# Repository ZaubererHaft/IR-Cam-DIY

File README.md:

# DIY IR Camera based on the MLX90640 IR sensor array

## Hardware

### Schematic

### Layout

### Chassis

## Software

### Display

### USB

### Sensor

### Flash

## ToDos
* Implement Config file [x]
* Fix saved image [x]
* Activate upscaling when saving image
* Implement battery level with ADC3 [x]
* Implement auto range or definable range
* Fix warnings in user_interface.c
* Replace Error_Handler with a suited dialogue

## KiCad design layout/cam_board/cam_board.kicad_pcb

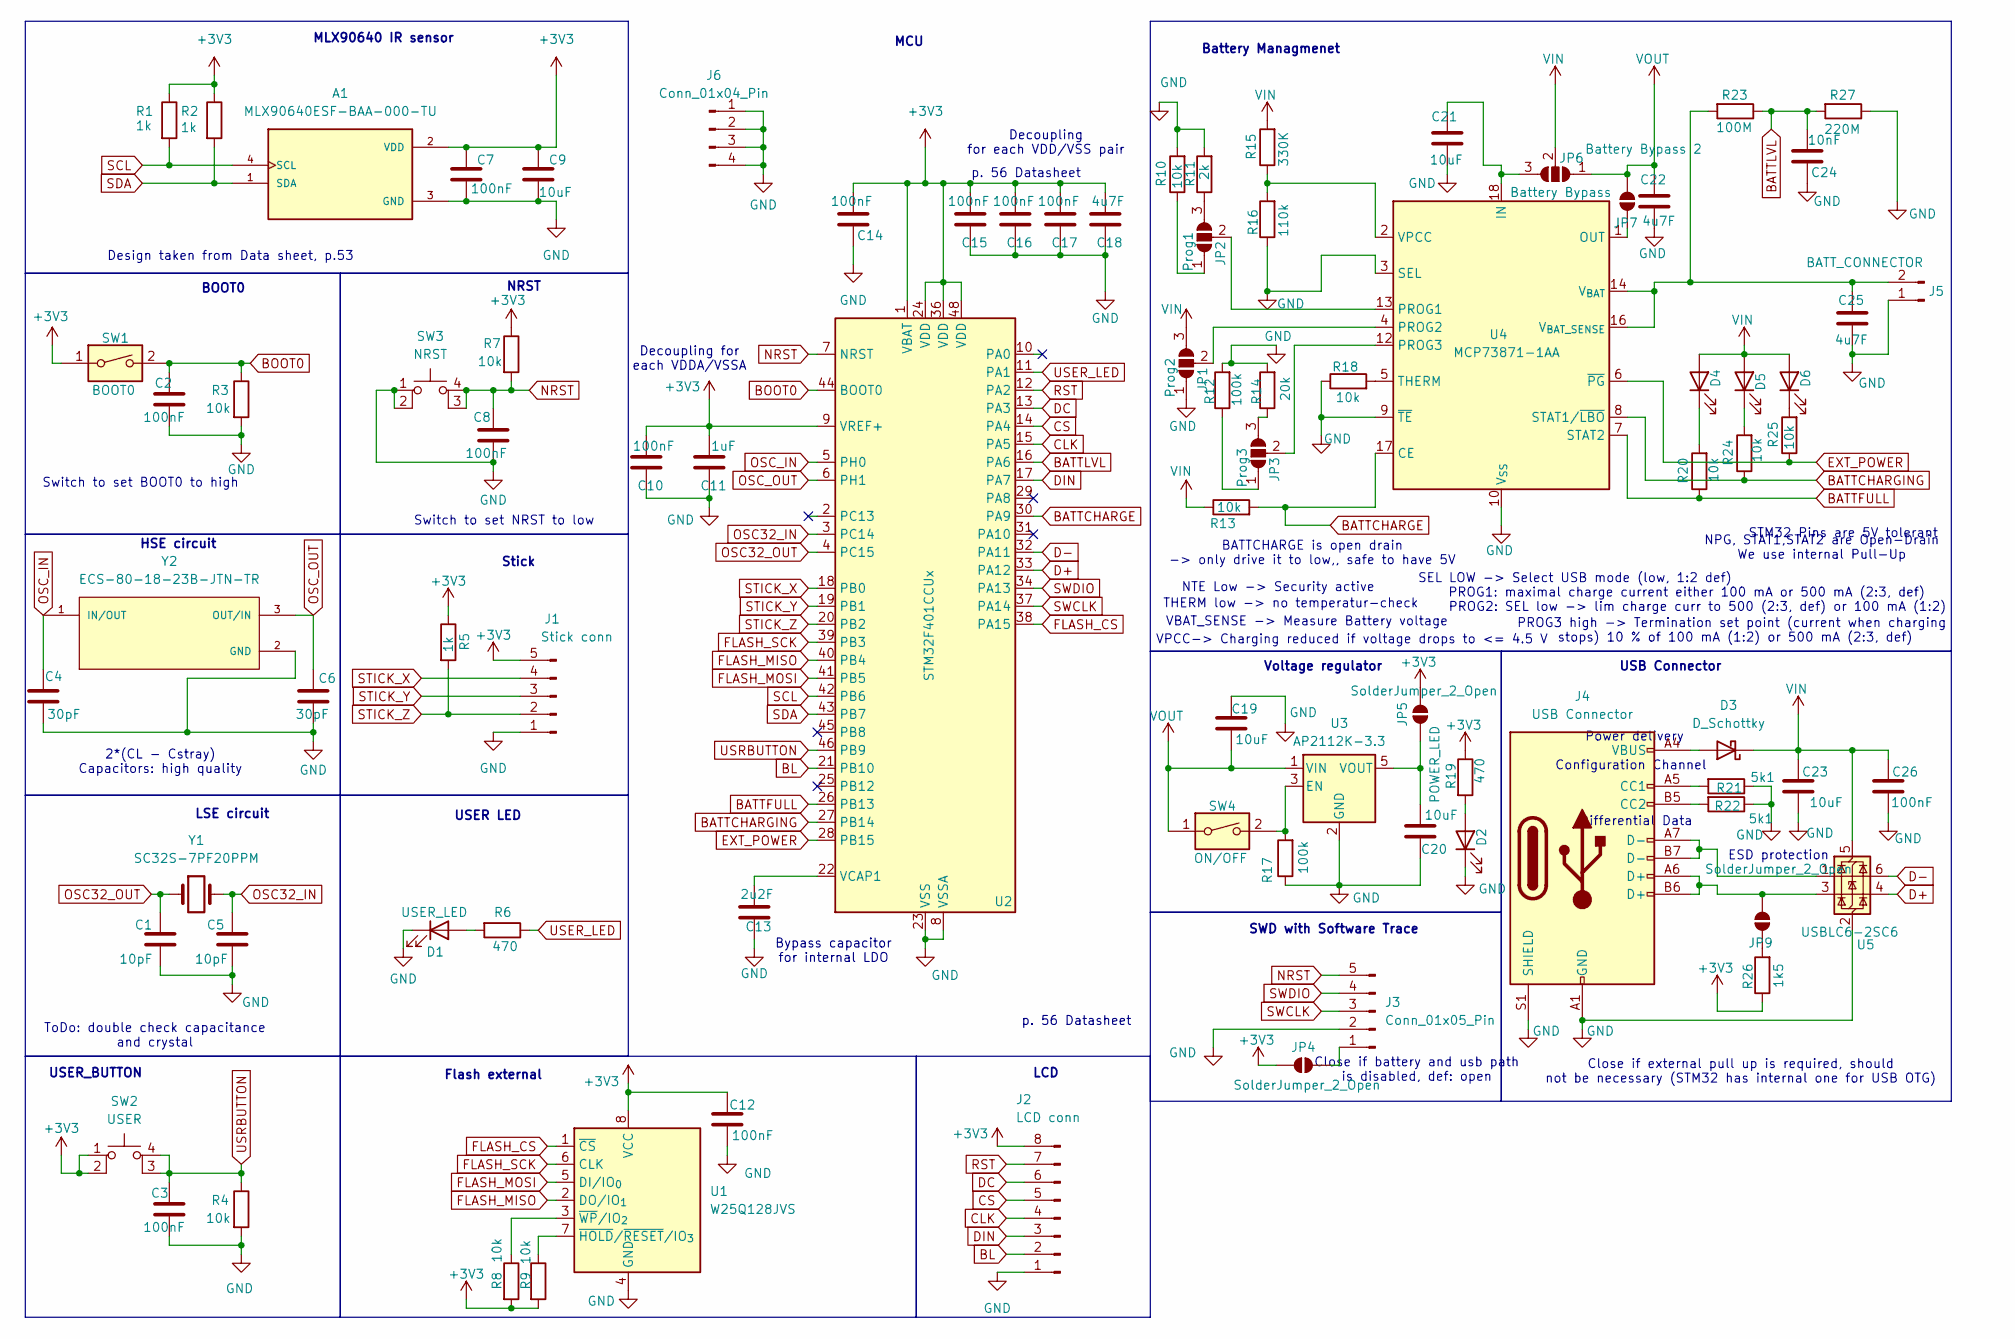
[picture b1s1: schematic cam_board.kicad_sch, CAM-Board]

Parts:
A1: MLX90640ESF-BAA-000-TU; TO292P930H600-4-MLX; PARTREV 11
C1, C5: 10pF; C_0603_1608Metric_Pad1.08x0.95mm_HandSolder
C2, C3, C7, C8, C10, C12, C14, C15, C16, C17, C26: 100nF; C_0603_1608Metric_Pad1.08x0.95mm_HandSolder
C4, C6: 30pF; C_0603_1608Metric_Pad1.08x0.95mm_HandSolder
C9, C19, C20, C21, C23: 10uF; C_0603_1608Metric_Pad1.08x0.95mm_HandSolder
C11: 1uF; C_0603_1608Metric_Pad1.08x0.95mm_HandSolder
C13: 2u2F; C_0603_1608Metric_Pad1.08x0.95mm_HandSolder
C18, C22, C25: 4u7F; C_0603_1608Metric_Pad1.08x0.95mm_HandSolder
C24: 10nF; C_0603_1608Metric_Pad1.08x0.95mm_HandSolder
D1: USER_LED; LED_0603_1608Metric_Pad1.05x0.95mm_HandSolder
D2, D4, D5, D6: POWER_LED; LED_0603_1608Metric_Pad1.05x0.95mm_HandSolder
D3: D_Schottky; D_0603_1608Metric_Pad1.05x0.95mm_HandSolder
J1: Stick conn; PinHeader_1x05_P2.54mm_Vertical
J2: LCD conn; PinHeader_1x08_P2.54mm_Vertical
J3: Conn_01x05_Pin; PinHeader_1x05_P2.54mm_Vertical
J4: USB Connector; USB_C_Receptacle_HRO_TYPE-C-31-M-12
J5: BATT_CONNECTOR; JST_PH_B2B-PH-K_1x02_P2.00mm_Vertical
J6: Conn_01x04_Pin; PinHeader_1x04_P2.54mm_Vertical
JP1: Prog2; SolderJumper-3_P1.3mm_Open_RoundedPad1.0x1.5mm_NumberLabels
JP2: Prog1; SolderJumper-3_P1.3mm_Open_RoundedPad1.0x1.5mm_NumberLabels
JP3: Prog3; SolderJumper-3_P1.3mm_Open_RoundedPad1.0x1.5mm_NumberLabels
JP4, JP5, JP9: SolderJumper_2_Open; SolderJumper-2_P1.3mm_Open_RoundedPad1.0x1.5mm
JP6: Battery Bypass; SolderJumper-3_P1.3mm_Open_RoundedPad1.0x1.5mm_NumberLabels
JP7: Battery Bypass 2; SolderJumper-2_P1.3mm_Open_RoundedPad1.0x1.5mm
R1, R2, R5: 1k; R_0603_1608Metric_Pad0.98x0.95mm_HandSolder
R3, R4, R7, R8, R9, R10, R13, R18, R20, R24, R25: 10k; R_0603_1608Metric_Pad0.98x0.95mm_HandSolder
R6, R19: 470; R_0603_1608Metric_Pad0.98x0.95mm_HandSolder
R11: 2k; R_0603_1608Metric_Pad0.98x0.95mm_HandSolder
R12, R17: 100k; R_0603_1608Metric_Pad0.98x0.95mm_HandSolder
R14: 20k; R_0603_1608Metric_Pad0.98x0.95mm_HandSolder
R15: 330K; R_0603_1608Metric_Pad0.98x0.95mm_HandSolder
R16: 110k; R_0603_1608Metric_Pad0.98x0.95mm_HandSolder
R21, R22: 5k1; R_0603_1608Metric_Pad0.98x0.95mm_HandSolder
R23: 100M; R_0603_1608Metric_Pad0.98x0.95mm_HandSolder
R26: 1k5; R_0603_1608Metric_Pad0.98x0.95mm_HandSolder
R27: 220M; R_0603_1608Metric_Pad0.98x0.95mm_HandSolder
SW1: BOOT0; SW_DIP_SPSTx01_Slide_9.78x4.72mm_W7.62mm_P2.54mm
SW2: USER; SW_1825910-6-4
SW3: NRST; SW_1825910-6-4
SW4: ON/OFF; SW_DIP_SPSTx01_Slide_9.78x4.72mm_W7.62mm_P2.54mm
U1: W25Q128JVS; SOIC-8_5.3x5.3mm_P1.27mm
U2: STM32F401CCUx; QFN-48-1EP_7x7mm_P0.5mm_EP5.6x5.6mm
U3: AP2112K-3.3; SOT-23-5_HandSoldering
U4: MCP73871-1AA; QFN-20-1EP_4x4mm_P0.5mm_EP2.5x2.5mm_ThermalVias
U5: USBLC6-2SC6; SOT-23-6_Handsoldering
Y1: SC32S-7PF20PPM; XTAL_CTS3-32.768-12.5-20-CT
Y2: ECS-80-18-23B-JTN-TR; XTAL_ECS-80-18-23B-JTN-TR

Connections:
+3V3: A1.2 (VDD), C7.2, C9.2, C10.2, C11.2, C12.2, C14.2, C15.2, C16.2, C17.2, C18.2, J1.5, J2.8, JP4.1 (A), JP5.2 (B), R1.1, R2.1, R5.1, R7.1, R8.2, R9.2, R19.1, R26.1, SW1.1, SW2.1, SW2.2, U1.8 (VCC), U2.1 (VBAT), U2.9 (VREF+), U2.24 (VDD), U2.36 (VDD), U2.48 (VDD)
BATTCHARGE: R13.2, U2.30 (PA9), U4.17 (CE)
BATTCHARGING: R24.1, U2.27 (PB14), U4.8 (STAT1/~LBO)
BATTFULL: R20.1, U2.26 (PB13), U4.7 (STAT2)
BATTLVL: C24.2, R23.1, R27.2, U2.16 (PA6)
BL: J2.2, U2.21 (PB10)
BOOT0: C2.2, R3.1, SW1.2, U2.44 (BOOT0)
CLK: J2.4, U2.15 (PA5)
CS: J2.5, U2.14 (PA4)
D+: U2.33 (PA12), U5.4 (I/O2)
D-: U2.32 (PA11), U5.6 (I/O1)
DC: J2.6, U2.13 (PA3)
DIN: J2.3, U2.17 (PA7)
EXT_POWER: R25.1, U2.28 (PB15), U4.6 (~PG)
FLASH_CS: U1.1 (~CS), U2.38 (PA15)
FLASH_MISO: U1.2 (DO/IO_{1}), U2.40 (PB4)
FLASH_MOSI: U1.5 (DI/IO_{0}), U2.41 (PB5)
FLASH_SCK: U1.6 (CLK), U2.39 (PB3)
GND: A1.3 (GND), C1.1, C2.1, C3.1, C4.1, C5.1, C6.1, C7.1, C8.1, C9.1, C10.1, C11.1, C12.1, C13.1, C14.1, C15.1, C16.1, C17.1, C18.1, C19.2, C20.2, C21.1, C22.1, C23.1, C24.1, C25.1, C26.1, D1.1 (K), D2.1 (K), J1.1, J2.1, J3.2, J4.A1 (GND), J4.A12 (GND), J4.B1 (GND), J4.B12 (GND), J4.S1 (SHIELD), J5.1, J6.1, J6.2, J6.3, J6.4, JP1.1 (A), R3.2, R4.2, R10.2, R11.2, R12.2, R14.2, R16.1, R17.1, R18.1, R21.1, R22.1, R27.1, SW3.1, SW3.2, U1.4 (GND), U2.8 (VSSA), U2.23 (VSS), U2.35 (VSS), U2.47 (VSS), U2.49 (VSS), U3.2 (GND), U4.3 (SEL), U4.9 (~TE), U4.10 (V_{SS}), U4.11 (V_{SS}), U4.21 (V_{SS}), U5.2 (GND), Y2.2 (GND), Y2.4 (GND)
NRST: C8.2, J3.5, R7.2, SW3.3 (K), SW3.4 (A), U2.7 (NRST)
unnamed: D1.2 (A), R6.2
unnamed: D2.2 (A), R19.2
unnamed: D3.2 (A), J4.A4 (VBUS), J4.A9 (VBUS), J4.B4 (VBUS), J4.B9 (VBUS)
unnamed: D4.1 (K), R20.2
unnamed: D5.1 (K), R24.2
unnamed: D6.1 (K), R25.2
unnamed: J3.1, JP4.2 (B)
unnamed: J4.A5 (CC1), R21.2
unnamed: J4.B5 (CC2), R22.2
unnamed: J4.A7 (D-), J4.B7 (D-), U5.1 (I/O1)
unnamed: C25.2, J5.2, R23.2, U4.14 (V_{BAT}), U4.15 (V_{BAT}), U4.16 (V_{BAT_SENSE})
unnamed: JP1.2 (C), U4.4 (PROG2)
unnamed: JP2.1 (A), R10.1
unnamed: JP2.3 (B), R11.1
unnamed: JP2.2 (C), U4.13 (PROG1)
unnamed: JP3.1 (A), R12.1
unnamed: JP3.3 (B), R14.1
unnamed: JP3.2 (C), U4.12 (PROG3)
unnamed: C20.1, JP5.1 (A), U3.5 (VOUT)
unnamed: C21.2, JP6.3 (B), U4.18 (IN), U4.19 (IN)
unnamed: JP7.1 (A), U4.1 (OUT), U4.20 (OUT)
unnamed: JP9.1 (A), R26.2
unnamed: J4.A6 (D+), J4.B6 (D+), JP9.2 (B), U5.3 (I/O2)
unnamed: R9.1, U1.7 (~HOLD/~RESET/IO_{3})
unnamed: R8.1, U1.3 (~WP/IO_{2})
unnamed: C13.2, U2.22 (VCAP1)
unnamed: R17.2, SW4.2, U3.3 (EN)
unnamed: R18.2, U4.5 (THERM)
unnamed: R15.1, R16.2, U4.2 (VPCC)
OSC32_IN: C5.2, U2.3 (PC14), Y1.2
OSC32_OUT: C1.2, U2.4 (PC15), Y1.1
OSC_IN: C4.2, U2.5 (PH0), Y2.1 (IN/OUT)
OSC_OUT: C6.2, U2.6 (PH1), Y2.3 (OUT/IN)
RST: J2.7, U2.12 (PA2)
SCL: A1.4 (SCL), R1.2, U2.42 (PB6)
SDA: A1.1 (SDA), R2.2, U2.43 (PB7)
STICK_X: J1.4, U2.18 (PB0)
STICK_Y: J1.3, U2.19 (PB1)
STICK_Z: J1.2, R5.2, U2.20 (PB2)
SWCLK: J3.3, U2.37 (PA14)
SWDIO: J3.4, U2.34 (PA13)
USER_LED: R6.1, U2.11 (PA1)
USRBUTTON: C3.2, R4.1, SW2.3 (K), SW2.4 (A), U2.46 (PB9)
VIN: C23.2, C26.2, D3.1 (K), D4.2 (A), D5.2 (A), D6.2 (A), JP1.3 (B), JP6.2 (C), R13.1, R15.2, U5.5 (VBUS)
VOUT: C19.1, C22.2, JP6.1 (A), JP7.2 (B), SW4.1, U3.1 (VIN)

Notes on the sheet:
USER LED
NPG, STAT1,STAT2 are Open-Drain We use internal Pull-Up
PROG2: SEL low -> lim charge curr to 500 (2:3, def) or 100 mA (1:2)
Flash external
Voltage regulator
p. 56 Datasheet
SWD with Software Trace
THERM low -> no temperatur-check
NTE Low -> Security active
Stick
Decoupling for each VDDA/VSSA
Switch to set NRST to low
BOOT0
VPCC-> Charging reduced if voltage drops to <= 4.5 V
Battery Managmenet
SEL LOW -> Select USB mode (low, 1:2 def)
Configuration Channel
Power delivery
USB Connector
ESD protection
ToDo: double check capacitance and crystal
Close if battery and usb path is disabled, def: open
PROG1: maximal charge current either 100 mA or 500 mA (2:3, def)
Switch to set BOOT0 to high
Decoupling for each VDD/VSS pair
Design taken from Data sheet, p.53
2*(CL - Cstray) Capacitors: high quality
USER_BUTTON
MLX90640 IR sensor
HSE circuit
LSE circuit
MCU
BATTCHARGE is open drain -> only drive it to low,, safe to have 5V
Differential Data
Close if external pull up is required, should not be necessary (STM32 has internal one for USB OTG)
PROG3 high -> Termination set point (current when charging stops) 10 % of 100 mA (1:2) or 500 mA (2:3, def)
VBAT_SENSE -> Measure Battery voltage
STM32 Pins are 5V tolerant
LCD
Bypass capacitor for internal LDO

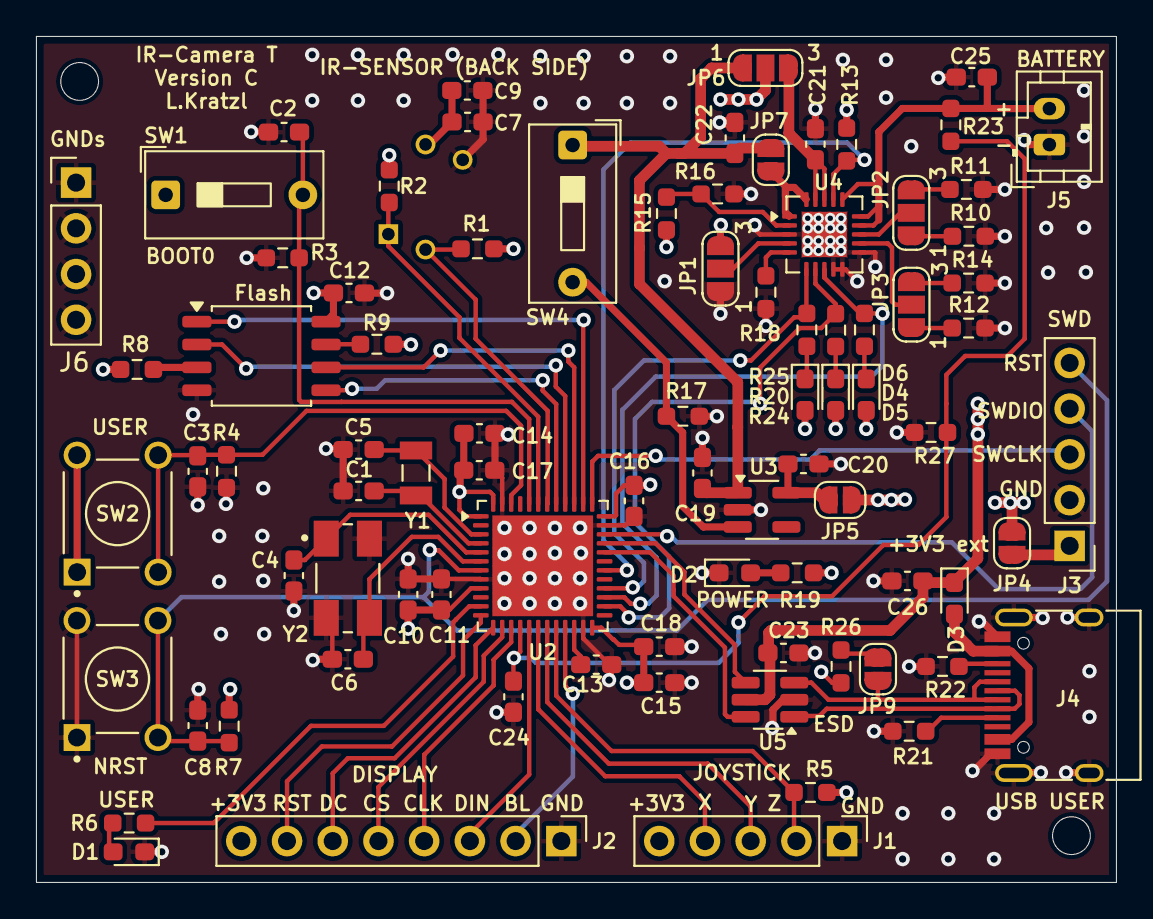
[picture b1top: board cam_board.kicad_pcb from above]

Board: 4 copper layers, 60.0 x 47.0 mm, 87 parts (1 on the bottom side), 65 nets.

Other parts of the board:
M1, M2: MountingHole_2.1mm

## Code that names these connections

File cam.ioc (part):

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Mcu.Name=STM32F401C(B-C)Ux
Mcu.Package=UFQFPN48
Mcu.UserName=STM32F401CCUx
PA1.GPIOParameters=GPIO_Label
PA1.GPIO_Label=USER_LED
PA1.Signal=GPIO_Output
PA11.Mode=Device_Only
PA11.Signal=USB_OTG_FS_DM
PA12.Mode=Device_Only
PA12.Signal=USB_OTG_FS_DP
PA13.Mode=Serial_Wire
PA13.Signal=SYS_JTMS-SWDIO
PA14.Mode=Serial_Wire
PA14.Signal=SYS_JTCK-SWCLK
PA15.GPIOParameters=GPIO_Speed,PinState,GPIO_PuPd,GPIO_Label
PA15.GPIO_Label=FLASH_CS
PA15.GPIO_PuPd=GPIO_NOPULL
PA15.GPIO_Speed=GPIO_SPEED_FREQ_VERY_HIGH
PA15.PinState=GPIO_PIN_SET
PA15.Signal=GPIO_Output
PA2.GPIOParameters=GPIO_Label
PA2.GPIO_Label=RST
PA2.Signal=GPIO_Output
PA3.GPIOParameters=GPIO_Label
PA3.GPIO_Label=DC
PA3.Signal=GPIO_Output
PA4.GPIOParameters=GPIO_Label
PA4.GPIO_Label=CS
PA4.Signal=GPIO_Output
PA5.GPIOParameters=GPIO_Label
PA5.GPIO_Label=CLK
PA5.Mode=TX_Only_Simplex_Unidirect_Master
PA5.Signal=SPI1_SCK
PA6.GPIOParameters=GPIO_Label
PA6.GPIO_Label=BATTLVL
PA6.Signal=ADCx_IN6
PA7.GPIOParameters=GPIO_Label
PA7.GPIO_Label=DIN
PA7.Mode=TX_Only_Simplex_Unidirect_Master
PA7.Signal=SPI1_MOSI
PA9.GPIOParameters=GPIO_Speed,PinState,GPIO_PuPd,GPIO_Label,GPIO_ModeDefaultOutputPP
PA9.GPIO_Label=BATTCHARGE
PA9.GPIO_ModeDefaultOutputPP=GPIO_MODE_OUTPUT_OD
PA9.GPIO_PuPd=GPIO_NOPULL
PA9.GPIO_Speed=GPIO_SPEED_FREQ_LOW
PA9.PinState=GPIO_PIN_SET
PA9.Signal=GPIO_Output
PB0.GPIOParameters=GPIO_Label
PB0.GPIO_Label=STICK_X
PB0.Signal=ADCx_IN8
PB1.GPIOParameters=GPIO_Label
PB1.GPIO_Label=STICK_Y
PB1.Signal=ADCx_IN9
PB10.GPIOParameters=GPIO_Label
PB10.GPIO_Label=BL
PB10.Signal=S_TIM2_CH3
PB13.GPIOParameters=GPIO_PuPd,GPIO_Label
PB13.GPIO_Label=BATTFULL
PB13.GPIO_PuPd=GPIO_PULLUP
PB13.Signal=GPIO_Input
PB14.GPIOParameters=GPIO_PuPd,GPIO_Label
PB14.GPIO_Label=BATTCHARGING
PB14.GPIO_PuPd=GPIO_PULLUP
PB14.Signal=GPIO_Input
PB15.GPIOParameters=GPIO_PuPd,GPIO_Label
PB15.GPIO_Label=EXT_POWER
PB15.GPIO_PuPd=GPIO_PULLUP
PB15.Signal=GPIO_Input
PB2.GPIOParameters=GPIO_PuPd,GPIO_Label,GPIO_ModeDefaultEXTI
PB2.GPIO_Label=STICK_Z
PB2.GPIO_ModeDefaultEXTI=GPIO_MODE_IT_FALLING
PB2.GPIO_PuPd=GPIO_NOPULL
PB2.Signal=GPXTI2
PB3.GPIOParameters=GPIO_Label
PB3.GPIO_Label=FLASH_SCK
PB3.Mode=Full_Duplex_Master
PB3.Signal=SPI3_SCK
PB4.GPIOParameters=GPIO_Label
PB4.GPIO_Label=FLASH_MISO
PB4.Mode=Full_Duplex_Master
PB4.Signal=SPI3_MISO
PB5.GPIOParameters=GPIO_Label
PB5.GPIO_Label=FLASH_MOSI
PB5.Mode=Full_Duplex_Master
PB5.Signal=SPI3_MOSI
PB6.GPIOParameters=GPIO_Label
PB6.GPIO_Label=SCL
PB6.Mode=I2C
PB6.Signal=I2C1_SCL
PB7.GPIOParameters=GPIO_Label
PB7.GPIO_Label=SDA
PB7.Mode=I2C
PB7.Signal=I2C1_SDA
PB9.GPIOParameters=GPIO_Label
PB9.GPIO_Label=USRBUTTON
PB9.Signal=GPXTI9
PC14-OSC32_IN.Mode=LSE-External-Oscillator
PC14-OSC32_IN.Signal=RCC_OSC32_IN
PC15-OSC32_OUT.Mode=LSE-External-Oscillator
PC15-OSC32_OUT.Signal=RCC_OSC32_OUT
PH0\ -\ OSC_IN.Mode=HSE-External-Oscillator
PH0\ -\ OSC_IN.Signal=RCC_OSC_IN
PH1\ -\ OSC_OUT.Mode=HSE-External-Oscillator
PH1\ -\ OSC_OUT.Signal=RCC_OSC_OUT
RCC.HSE_VALUE=8000000
RCC.SYSCLKFreq_VALUE=84000000
RCC.SYSCLKSource=RCC_SYSCLKSOURCE_PLLCLK
board=custom

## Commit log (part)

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2026-01-01 First prototype
2026-01-02 Update lib
2026-01-02 Update UI
2026-01-02 add heatmap.c
2026-01-03 Several optimizations and button to switch between record and no record
2026-01-03 Add heatmaps
2026-01-03 Heatmap is now dynamic
2026-01-03 Add WFI
2026-01-05 Prepare upscaling
2026-01-05 Reduce refresh rate and read all sub-pages in the upscaling case
2026-01-07 Some performance optimization
2026-01-07 Prepare FPS display
2026-01-08 Further optimizations (getting close to 15 Hz)
2026-01-08 Better heat map
2026-01-11 First DMA attempt
2026-01-11 Fix missing LSB correction
2026-01-11 Fix missing swap of pages
2026-01-11 Adjust redrawing threshold
2026-01-11 Add upscale
2026-01-11 Remove error handling
2026-01-16 Prepare joy stick
2026-01-17 Prototype of menu
2026-01-17 Update menu
2026-01-18 Now use I2C3 instead of I2C2 to use debug trace
2026-01-18 Update layout and schematic
2026-01-20 First full schematic
2026-02-01 Update to new layout
2026-02-01 Add gitignore
2026-02-08 Fix menu, add missing pull-up
2026-02-08 Initiate refactoring
2026-02-08 Migrate to new CubeMX version
2026-02-08 Prepare refactoring
2026-02-08 Fix stick y
2026-02-13 Prepare USB and fix missing GND line in layout
2026-02-14 Update board and layout
2026-02-14 CAM is now using I2C1, add SPI for flash
2026-02-14 Prepare SPI flash
2026-02-15 First refactored version
2026-02-15 Add generic write function
2026-02-15 Refactor generic write
2026-02-15 Try to synch flash
2026-02-15 First working version
2026-02-16 add to main loop, update layout and schematic
2026-02-18 Add FATFS to write files
2026-02-20 Try to refactor again
2026-02-20 Remove delay
2026-02-20 Fix warnings
2026-02-20 Add wait for ready
2026-02-21 Clean up driver
2026-02-22 Add comment
2026-02-22 FS is now created by MCU
2026-03-01 Update layout
2026-05-22 Changed foot print to 0603 for allk capacitors Changed footprints for connectors to 2.54 mm Fixed footprint of 32 MHz crystal / Y1 Change slider footprint from SMD to THT Remove USB pull up 1k5 Intro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
2026-06-04 Update / version B
2026-06-13 Add optional USB pullup, add more LEDs
2026-06-14 External clock is now 8 MHz
2026-06-16 Prepare SW update
